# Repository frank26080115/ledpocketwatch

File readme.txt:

See http://www.frank-zhao.com/ledpocketwatch/ for more details

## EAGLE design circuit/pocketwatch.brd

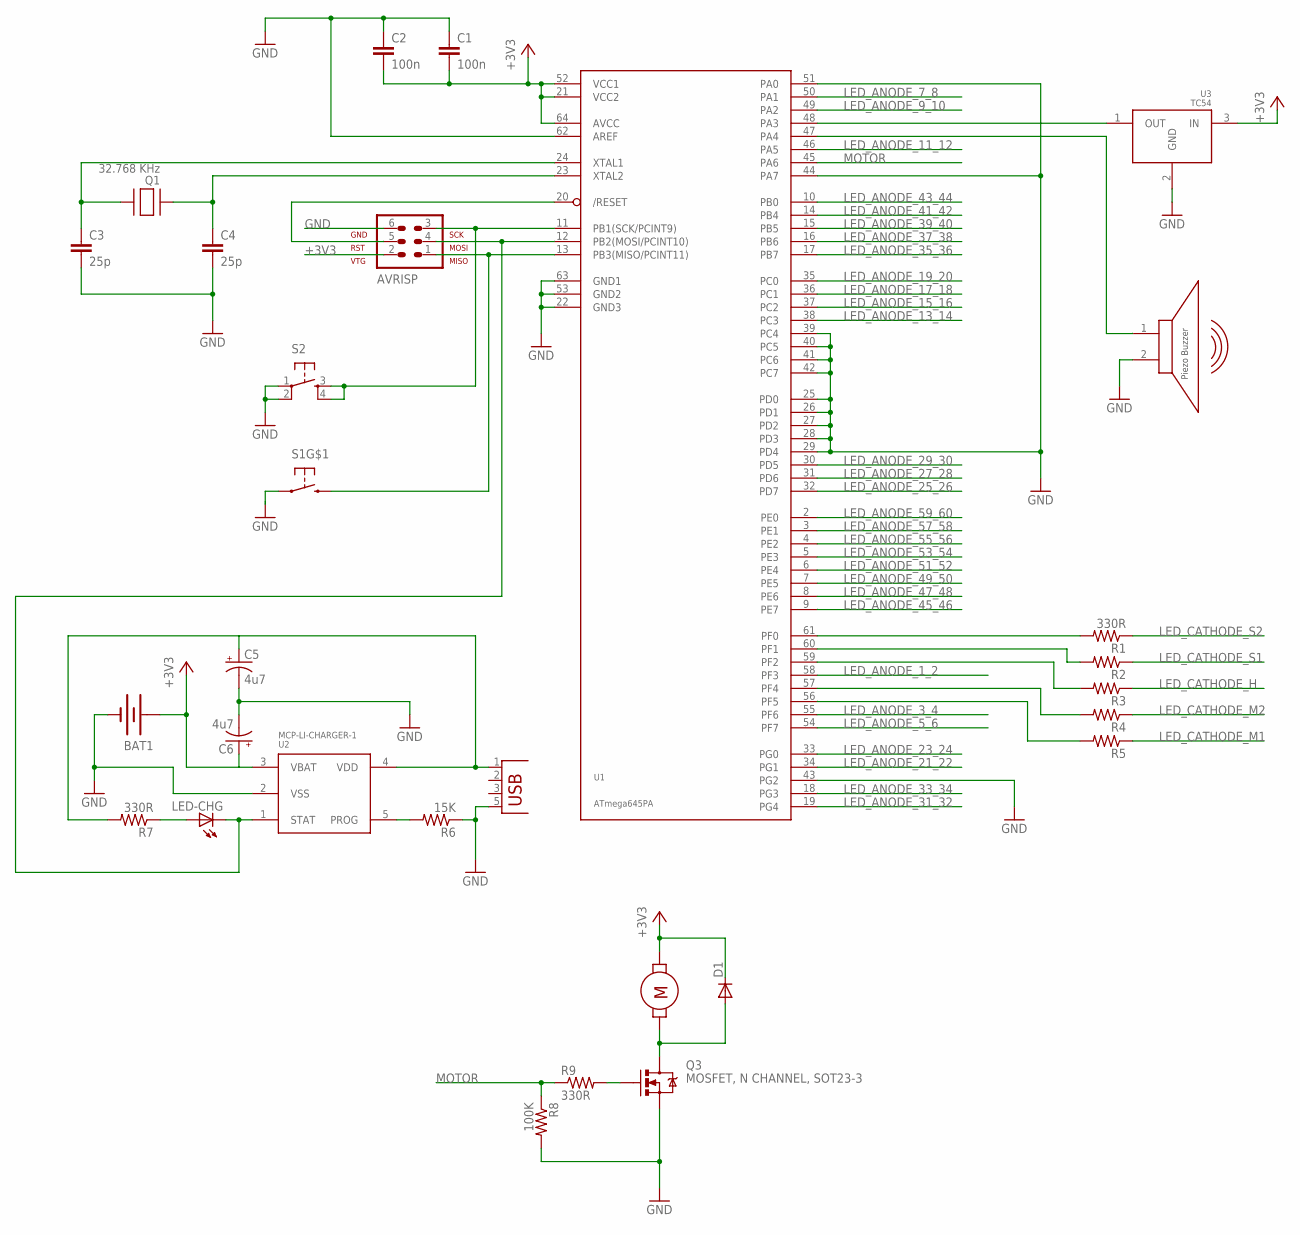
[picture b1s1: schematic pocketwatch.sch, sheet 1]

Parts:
AVRISP: AVR-ISP-6
BAT1: BATTERY245MM; BATTCON_245MM
C1, C2: 100n; C0603
C3, C4: 25p; C0603
C5, C6: 4u7; SMC_A
D1: DIODESOD; SOD-323
LED-CHG: LEDCHIPLED_0603; CHIPLED_0603
M1: MOTOR; VIBRATION-MOTOR
Q1: 32.768 KHz; XTAL_2SMD
Q2: BUZZER; BUZZER_1
Q3: MOSFET, N CHANNEL, SOT23-3; SOT23-3
R1, R7, R9: 330R; R0603
R2, R3, R4, R5: R-US_R0603; R0603
R6: 15K; R0603
R8: 100K; R0603
S1: TAC_SWITCH_SINGLE; TAC_SWITCH_SIDE_1
S2: TAC_SWITCHSMD; TACTILE_SWITCH_SMD
U1: ATmega645PA; TQFP64
U2: MCP-LI-CHARGER-1; SOT23-5
U3: TC54; SOT23-3
X1: USB-MICRO_B; USB_MICRO_B

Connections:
+3V3: AVRISP.2 (VTG), BAT1.1 (+), C1.2, C2.2, C6.+, D1.1 (C), M1.P$1, U1.21 (VCC2), U1.52 (VCC1), U1.64 (AVCC), U2.3 (VBAT), U3.3 (IN)
GND: AVRISP.6 (GND), BAT1.2 (-), C1.1, C2.1, C3.2, C4.2, C5.-, C6.-, Q2.2, Q3.2 (S), R6.1, R8.2, S1.G1, S1.G2, S1.P$2 (1), S2.1, S2.2, U1.22 (GND3), U1.25 (PD0), U1.26 (PD1), U1.27 (PD2), U1.28 (PD3), U1.29 (PD4), U1.39 (PC4), U1.40 (PC5), U1.41 (PC6), U1.42 (PC7), U1.43 (PG2), U1.44 (PA7), U1.51 (PA0), U1.53 (GND2), U1.62 (AREF), U1.63 (GND1), U2.2 (VSS), U3.2 (GND), X1.5 (GND), X1.P$3, X1.P$4, X1.P$7, X1.P$8
LED_ANODE_1_2: U1.58 (PF3); also elsewhere on the board
LED_ANODE_3_4: U1.55 (PF6); also elsewhere on the board
LED_ANODE_5_6: U1.54 (PF7); also elsewhere on the board
LED_ANODE_7_8: U1.50 (PA1); also elsewhere on the board
LED_ANODE_9_10: U1.49 (PA2); also elsewhere on the board
LED_ANODE_11_12: U1.46 (PA5); also elsewhere on the board
LED_ANODE_13_14: U1.38 (PC3); also elsewhere on the board
LED_ANODE_15_16: U1.37 (PC2); also elsewhere on the board
LED_ANODE_17_18: U1.36 (PC1); also elsewhere on the board
LED_ANODE_19_20: U1.35 (PC0); also elsewhere on the board
LED_ANODE_21_22: U1.34 (PG1); also elsewhere on the board
LED_ANODE_23_24: U1.33 (PG0); also elsewhere on the board
LED_ANODE_25_26: U1.32 (PD7); also elsewhere on the board
LED_ANODE_27_28: U1.31 (PD6); also elsewhere on the board
LED_ANODE_29_30: U1.30 (PD5); also elsewhere on the board
LED_ANODE_31_32: U1.19 (PG4); also elsewhere on the board
LED_ANODE_33_34: U1.18 (PG3); also elsewhere on the board
LED_ANODE_35_36: U1.17 (PB7); also elsewhere on the board
LED_ANODE_37_38: U1.16 (PB6); also elsewhere on the board
LED_ANODE_39_40: U1.15 (PB5); also elsewhere on the board
LED_ANODE_41_42: U1.14 (PB4); also elsewhere on the board
LED_ANODE_43_44: U1.10 (PB0); also elsewhere on the board
LED_ANODE_45_46: U1.9 (PE7); also elsewhere on the board
LED_ANODE_47_48: U1.8 (PE6); also elsewhere on the board
LED_ANODE_49_50: U1.7 (PE5); also elsewhere on the board
LED_ANODE_51_52: U1.6 (PE4); also elsewhere on the board
LED_ANODE_53_54: U1.5 (PE3); also elsewhere on the board
LED_ANODE_55_56: U1.4 (PE2); also elsewhere on the board
LED_ANODE_57_58: U1.3 (PE1); also elsewhere on the board
LED_ANODE_59_60: U1.2 (PE0); also elsewhere on the board
LED_CATHODE_H: R3.1; also elsewhere on the board
LED_CATHODE_M1: R5.1; also elsewhere on the board
LED_CATHODE_M2: R4.1; also elsewhere on the board
LED_CATHODE_S1: R2.1; also elsewhere on the board
LED_CATHODE_S2: R1.1; also elsewhere on the board
MOTOR: R8.1, R9.1, U1.45 (PA6)
unnamed: AVRISP.3 (SCK), S2.3, S2.4, U1.11 (PB1(SCK/PCINT9))
unnamed: D1.2 (A), M1.P$2, Q3.3 (D)
unnamed: AVRISP.1 (MISO), S1.P$1 (2), U1.13 (PB3(MISO/PCINT11))
unnamed: AVRISP.5 (RST), U1.20 (/RESET)
unnamed: R1.2, U1.61 (PF0)
unnamed: R2.2, U1.60 (PF1)
unnamed: C4.1, Q1.1, U1.23 (XTAL2)
unnamed: C3.1, Q1.2, U1.24 (XTAL1)
unnamed: R3.2, U1.59 (PF2)
unnamed: R4.2, U1.57 (PF4)
unnamed: R5.2, U1.56 (PF5)
unnamed: C5.+, R7.2, U2.4 (VDD), X1.1 (VBUS)
unnamed: R6.2, U2.5 (PROG)
unnamed: AVRISP.4 (MOSI), LED-CHG.C, U1.12 (PB2(MOSI/PCINT10)), U2.1 (STAT)
unnamed: LED-CHG.A, R7.1
unnamed: U1.48 (PA3), U3.1 (OUT)
unnamed: Q2.1, U1.47 (PA4)
unnamed: Q3.1 (G), R9.2

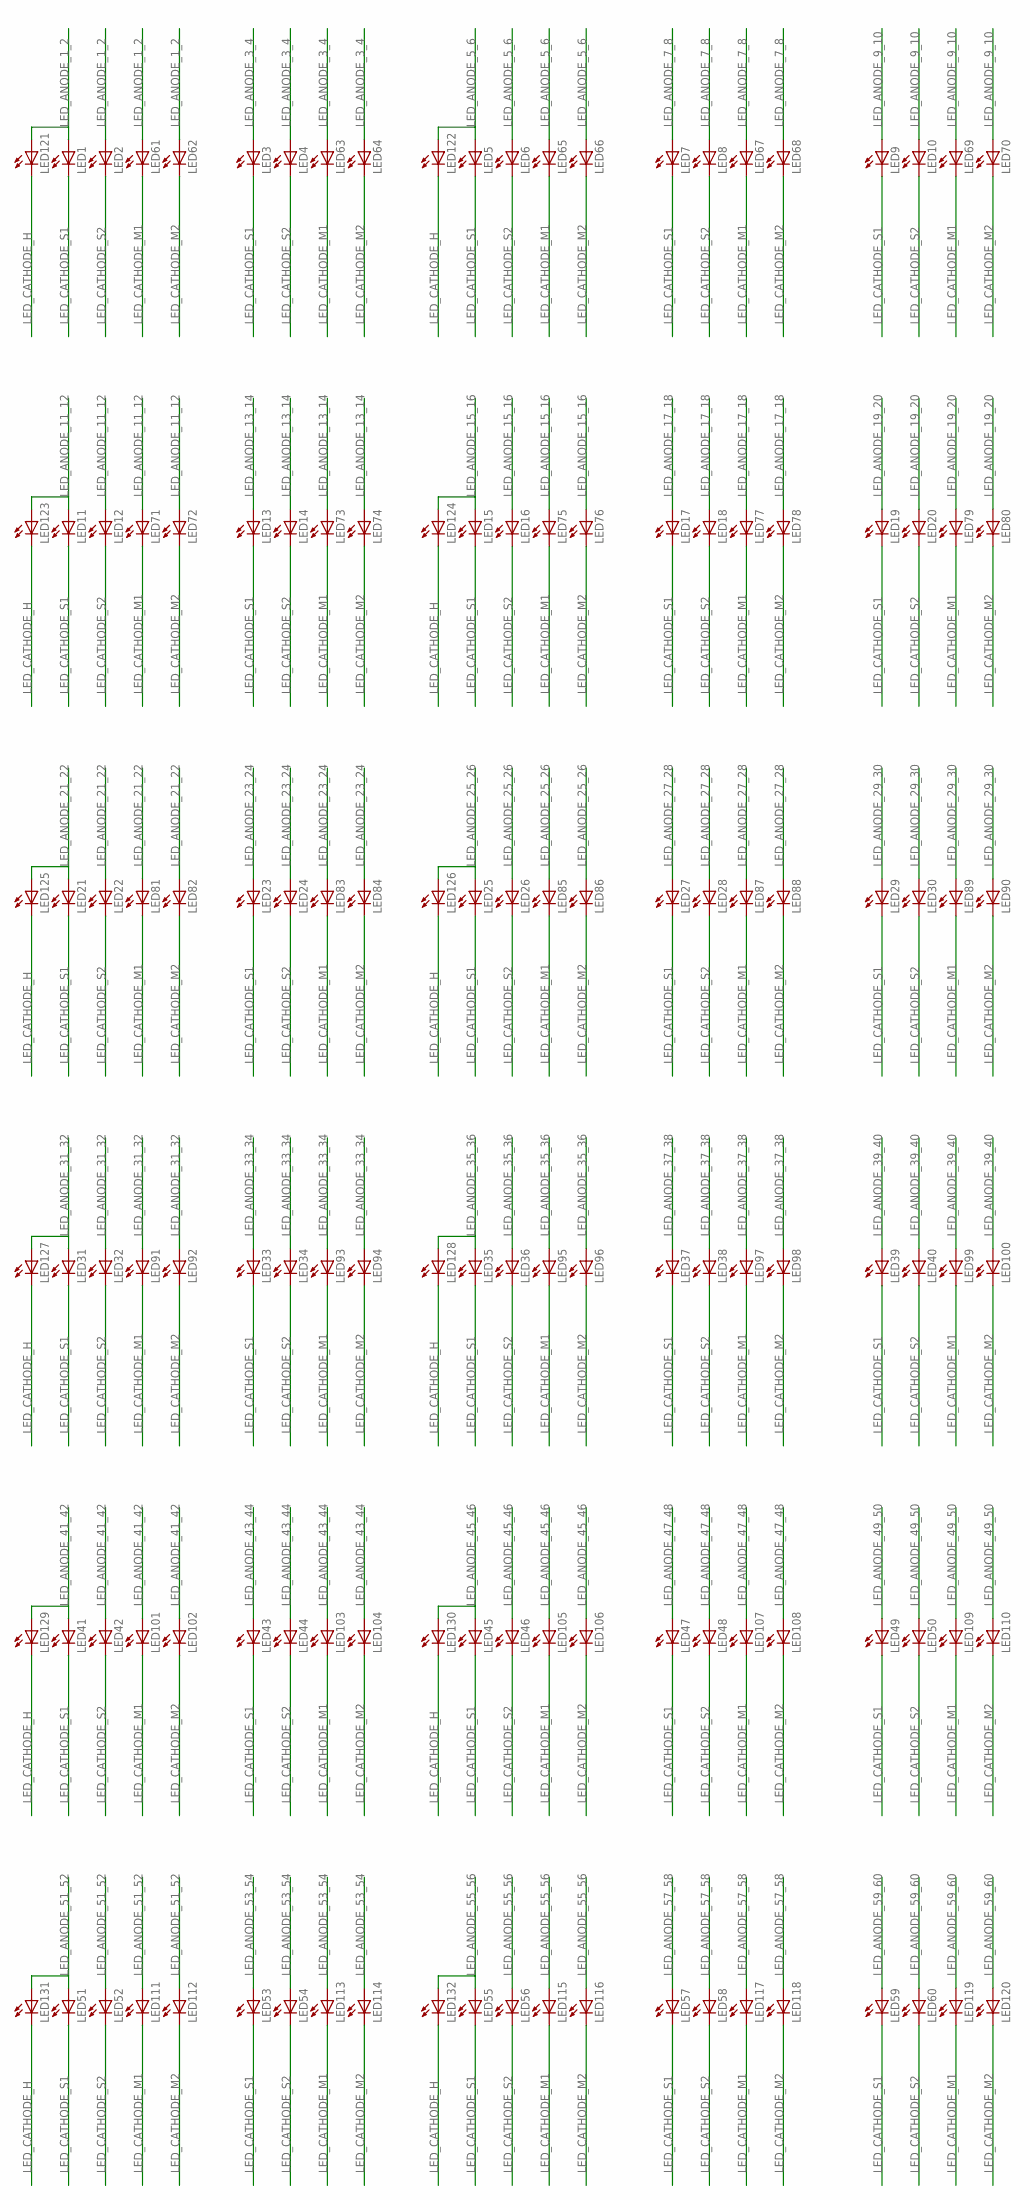
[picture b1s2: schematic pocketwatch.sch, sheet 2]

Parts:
LED1, LED2, LED3, LED4, LED5, LED6, LED7, LED8, LED9, LED10, LED11, LED12, LED13, LED14, LED15, LED16, LED17, LED18, LED19, LED20, LED21, LED22, LED23, LED24, LED25, LED26, LED27, LED28, LED29, LED30, LED31, LED32, LED33, LED34, LED35, LED36, LED37, LED38, LED39, LED40, LED41, LED42, LED43, LED44, LED45, LED46, LED47, LED48, LED49, LED50, LED51, LED52, LED53, LED54, LED55, LED56, LED57, LED58, LED59, LED60, LED61, LED62, LED63, LED64, LED65, LED66, LED67, LED68, LED69, LED70, LED71, LED72, LED73, LED74, LED75, LED76, LED77, LED78, LED79, LED80, LED81, LED82, LED83, LED84, LED85, LED86, LED87, LED88, LED89, LED90, LED91, LED92, LED93, LED94, LED95, LED96, LED97, LED98, LED99, LED100, LED101, LED102, LED103, LED104, LED105, LED106, LED107, LED108, LED109, LED110, LED111, LED112, LED113, LED114, LED115, LED116, LED117, LED118, LED119, LED120, LED121, LED122, LED123, LED124, LED125, LED126, LED127, LED128, LED129, LED130, LED131, LED132: LED_CHIPLED_0603_VIA_C; CHIPLED_0603_VIA_C

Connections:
LED_ANODE_1_2: LED1.A, LED2.A, LED61.A, LED62.A, LED121.A; also elsewhere on the board
LED_ANODE_3_4: LED3.A, LED4.A, LED63.A, LED64.A; also elsewhere on the board
LED_ANODE_5_6: LED5.A, LED6.A, LED65.A, LED66.A, LED122.A; also elsewhere on the board
LED_ANODE_7_8: LED7.A, LED8.A, LED67.A, LED68.A; also elsewhere on the board
LED_ANODE_9_10: LED9.A, LED10.A, LED69.A, LED70.A; also elsewhere on the board
LED_ANODE_11_12: LED11.A, LED12.A, LED71.A, LED72.A, LED123.A; also elsewhere on the board
LED_ANODE_13_14: LED13.A, LED14.A, LED73.A, LED74.A; also elsewhere on the board
LED_ANODE_15_16: LED15.A, LED16.A, LED75.A, LED76.A, LED124.A; also elsewhere on the board
LED_ANODE_17_18: LED17.A, LED18.A, LED77.A, LED78.A; also elsewhere on the board
LED_ANODE_19_20: LED19.A, LED20.A, LED79.A, LED80.A; also elsewhere on the board
LED_ANODE_21_22: LED21.A, LED22.A, LED81.A, LED82.A, LED125.A; also elsewhere on the board
LED_ANODE_23_24: LED23.A, LED24.A, LED83.A, LED84.A; also elsewhere on the board
LED_ANODE_25_26: LED25.A, LED26.A, LED85.A, LED86.A, LED126.A; also elsewhere on the board
LED_ANODE_27_28: LED27.A, LED28.A, LED87.A, LED88.A; also elsewhere on the board
LED_ANODE_29_30: LED29.A, LED30.A, LED89.A, LED90.A; also elsewhere on the board
LED_ANODE_31_32: LED31.A, LED32.A, LED91.A, LED92.A, LED127.A; also elsewhere on the board
LED_ANODE_33_34: LED33.A, LED34.A, LED93.A, LED94.A; also elsewhere on the board
LED_ANODE_35_36: LED35.A, LED36.A, LED95.A, LED96.A, LED128.A; also elsewhere on the board
LED_ANODE_37_38: LED37.A, LED38.A, LED97.A, LED98.A; also elsewhere on the board
LED_ANODE_39_40: LED39.A, LED40.A, LED99.A, LED100.A; also elsewhere on the board
LED_ANODE_41_42: LED41.A, LED42.A, LED101.A, LED102.A, LED129.A; also elsewhere on the board
LED_ANODE_43_44: LED43.A, LED44.A, LED103.A, LED104.A; also elsewhere on the board
LED_ANODE_45_46: LED45.A, LED46.A, LED105.A, LED106.A, LED130.A; also elsewhere on the board
LED_ANODE_47_48: LED47.A, LED48.A, LED107.A, LED108.A; also elsewhere on the board
LED_ANODE_49_50: LED49.A, LED50.A, LED109.A, LED110.A; also elsewhere on the board
LED_ANODE_51_52: LED51.A, LED52.A, LED111.A, LED112.A, LED131.A; also elsewhere on the board
LED_ANODE_53_54: LED53.A, LED54.A, LED113.A, LED114.A; also elsewhere on the board
LED_ANODE_55_56: LED55.A, LED56.A, LED115.A, LED116.A, LED132.A; also elsewhere on the board
LED_ANODE_57_58: LED57.A, LED58.A, LED117.A, LED118.A; also elsewhere on the board
LED_ANODE_59_60: LED59.A, LED60.A, LED119.A, LED120.A; also elsewhere on the board
LED_CATHODE_H: LED121.C, LED122.C, LED123.C, LED124.C, LED125.C, LED126.C, LED127.C, LED128.C, LED129.C, LED130.C, LED131.C, LED132.C; also elsewhere on the board
LED_CATHODE_M1: LED61.C, LED63.C, LED65.C, LED67.C, LED69.C, LED71.C, LED73.C, LED75.C, LED77.C, LED79.C, LED81.C, LED83.C, LED85.C, LED87.C, LED89.C, LED91.C, LED93.C, LED95.C, LED97.C, LED99.C, LED101.C, LED103.C, LED105.C, LED107.C, LED109.C, LED111.C, LED113.C, LED115.C, LED117.C, LED119.C; also elsewhere on the board
LED_CATHODE_M2: LED62.C, LED64.C, LED66.C, LED68.C, LED70.C, LED72.C, LED74.C, LED76.C, LED78.C, LED80.C, LED82.C, LED84.C, LED86.C, LED88.C, LED90.C, LED92.C, LED94.C, LED96.C, LED98.C, LED100.C, LED102.C, LED104.C, LED106.C, LED108.C, LED110.C, LED112.C, LED114.C, LED116.C, LED118.C, LED120.C; also elsewhere on the board
LED_CATHODE_S1: LED1.C, LED3.C, LED5.C, LED7.C, LED9.C, LED11.C, LED13.C, LED15.C, LED17.C, LED19.C, LED21.C, LED23.C, LED25.C, LED27.C, LED29.C, LED31.C, LED33.C, LED35.C, LED37.C, LED39.C, LED41.C, LED43.C, LED45.C, LED47.C, LED49.C, LED51.C, LED53.C, LED55.C, LED57.C, LED59.C; also elsewhere on the board
LED_CATHODE_S2: LED2.C, LED4.C, LED6.C, LED8.C, LED10.C, LED12.C, LED14.C, LED16.C, LED18.C, LED20.C, LED22.C, LED24.C, LED26.C, LED28.C, LED30.C, LED32.C, LED34.C, LED36.C, LED38.C, LED40.C, LED42.C, LED44.C, LED46.C, LED48.C, LED50.C, LED52.C, LED54.C, LED56.C, LED58.C, LED60.C; also elsewhere on the board

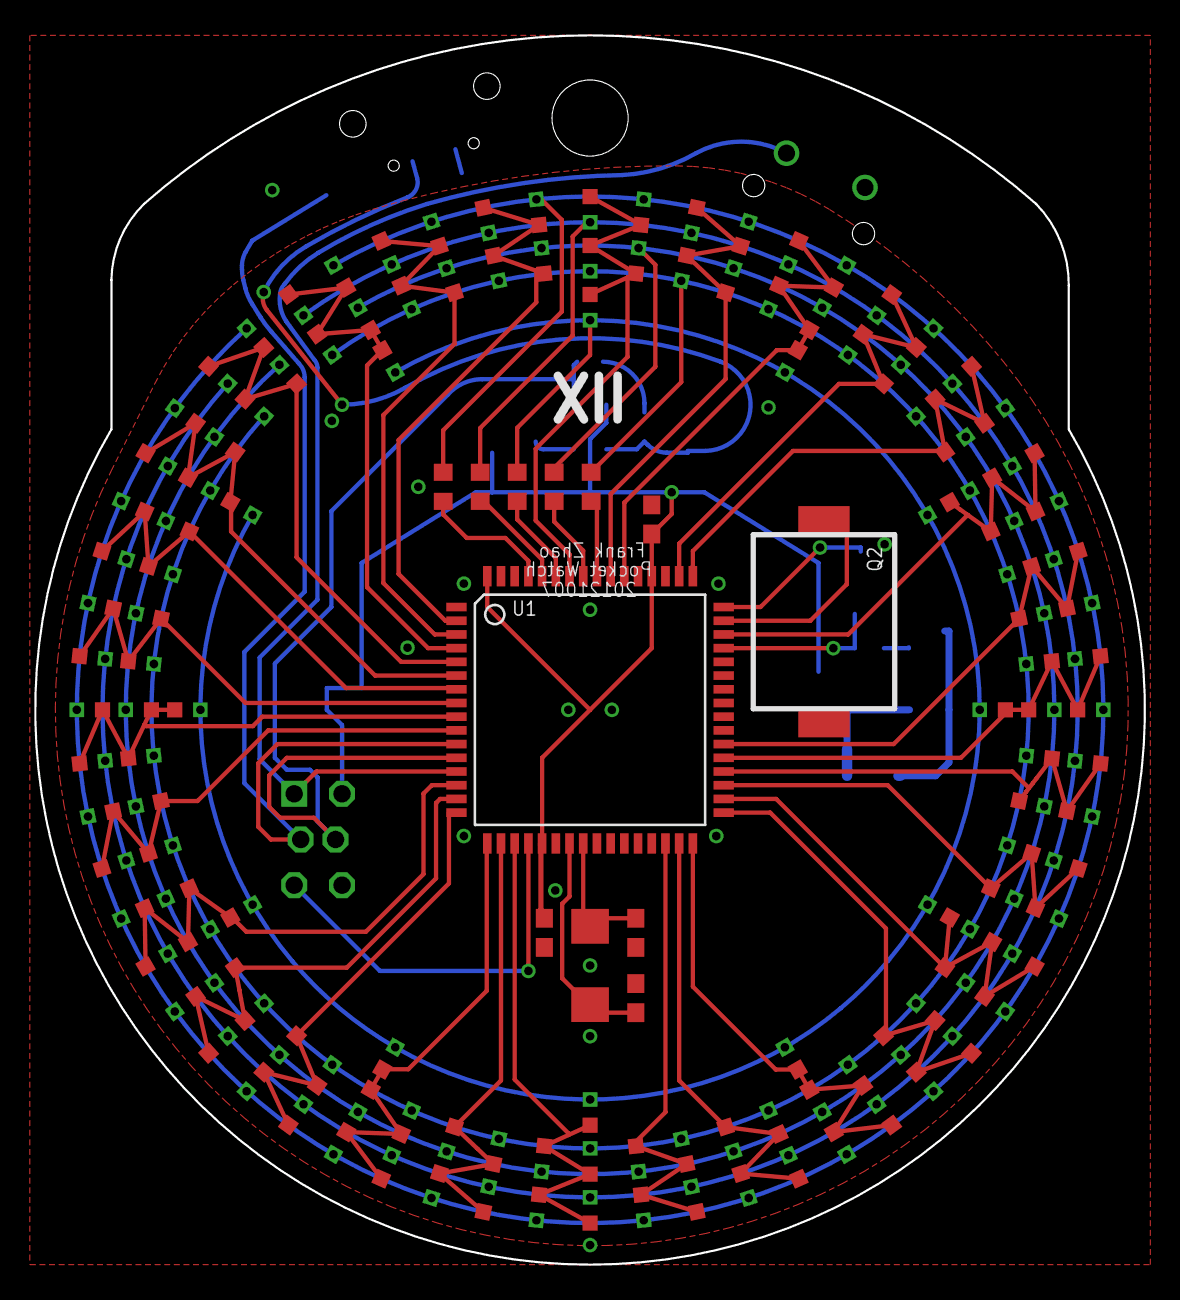
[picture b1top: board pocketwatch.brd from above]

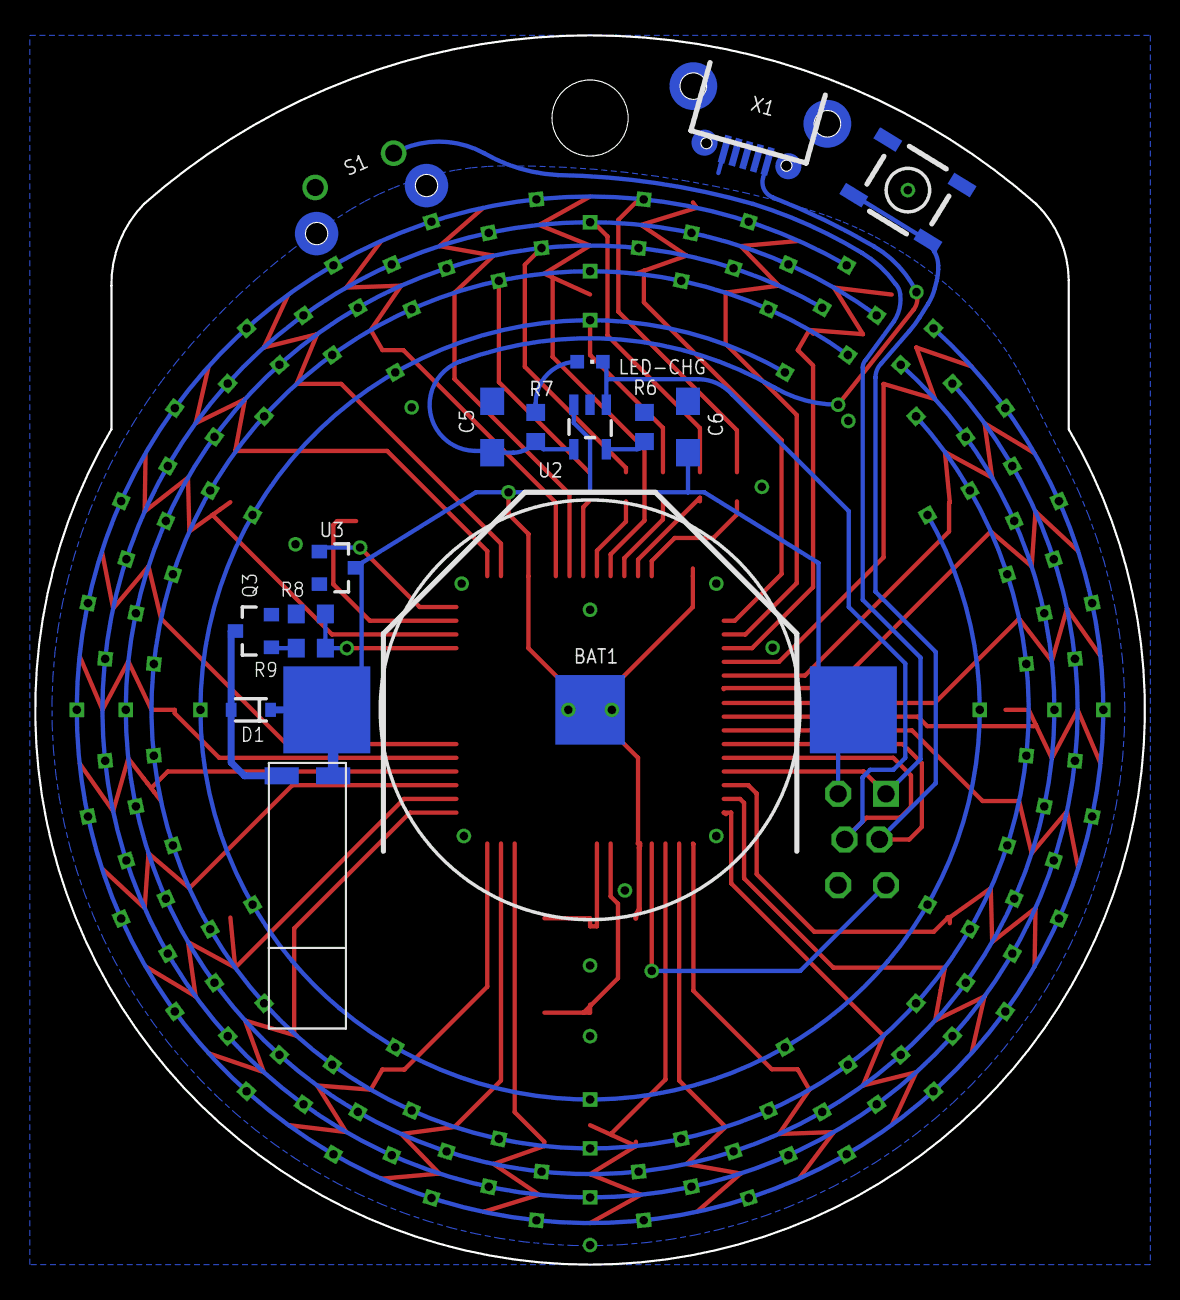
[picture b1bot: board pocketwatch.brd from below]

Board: 2 copper layers, 64.8 x 71.8 mm, 161 parts (16 on the bottom side), 56 nets.

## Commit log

2012-10-29 images deleted
2012-10-29 added parts list
2012-10-30 updated part list
2012-10-30 added test mode
2012-10-31 edited the main button in the 3D printed case
2012-10-31 deleted the atsuo file
2012-11-05 circuit maintainance
2012-11-05 3d maintainance
2012-11-05 changed code to something that actually works, will start improvments from here but this is the commit that will actually compile good
2012-11-05 added precompiled binary
2012-11-05 added copyright block
2012-11-05 introduced pocketwatch.h
2012-11-05 introduced the mode_t enum
2012-11-05 holding and timout threshold changed to defines
2012-11-05 corrected small bug regarding alarm setting, also motor tick works
2012-11-05 disable timer0 interrupt during sleep
2012-11-05 animation implemented but buggy so it's disabled
2012-11-11 screen on/off animation now working, fixed other stuff too
2012-11-12 added demo/random mode
2012-11-12 fixed some stuff, looks more like flow chart
